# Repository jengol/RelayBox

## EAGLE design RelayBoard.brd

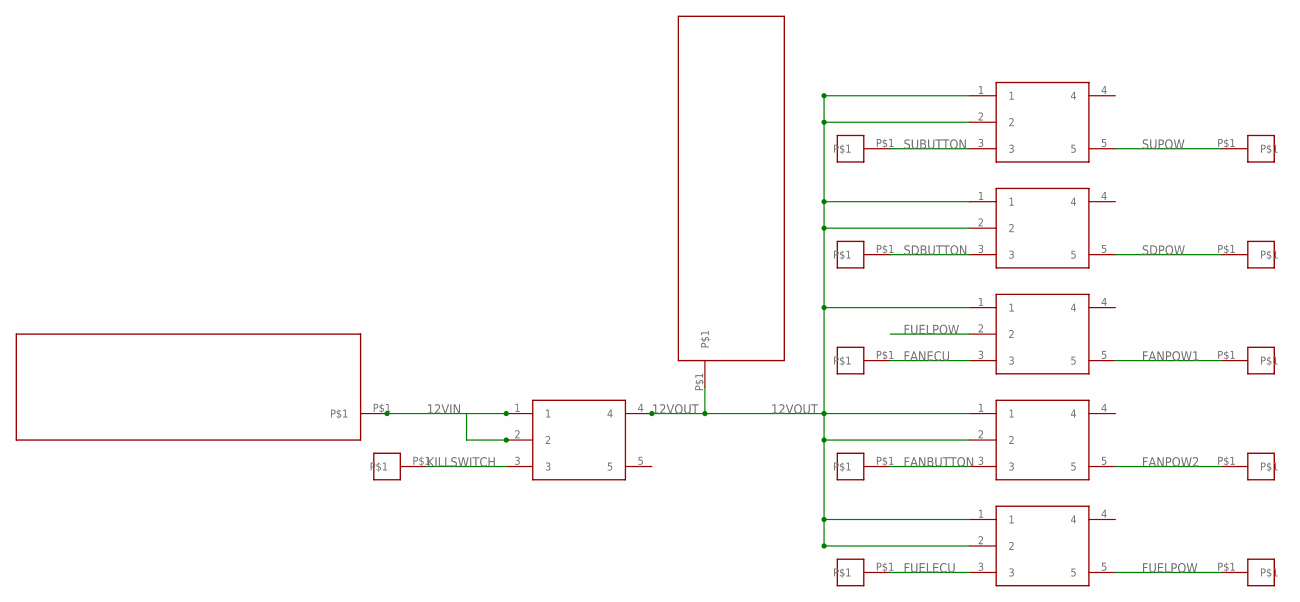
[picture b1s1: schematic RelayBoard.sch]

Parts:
U$1, U$2, U$3, U$4, U$5, U$6: RELAY
U$7, U$8: PLUG2
U$9, U$10, U$11, U$12, U$13, U$14, U$15, U$16, U$17, U$18, U$19: OUTPUT

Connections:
12VIN: U$6.1, U$6.2, U$7.P$1
12VOUT: U$1.1, U$1.2, U$2.1, U$2.2, U$3.1, U$4.1, U$4.2, U$5.1, U$5.2, U$6.4, U$8.P$1
FANBUTTON: U$4.3, U$11.P$1
FANECU: U$3.3, U$10.P$1
FANPOW1: U$3.5, U$16.P$1
FANPOW2: U$4.5, U$17.P$1
FUELECU: U$5.3, U$12.P$1
FUELPOW: U$3.2, U$5.5, U$18.P$1
KILLSWITCH: U$6.3, U$19.P$1
SDBUTTON: U$2.3, U$9.P$1
SDPOW: U$2.5, U$15.P$1
SUBUTTON: U$1.3, U$13.P$1
SUPOW: U$1.5, U$14.P$1

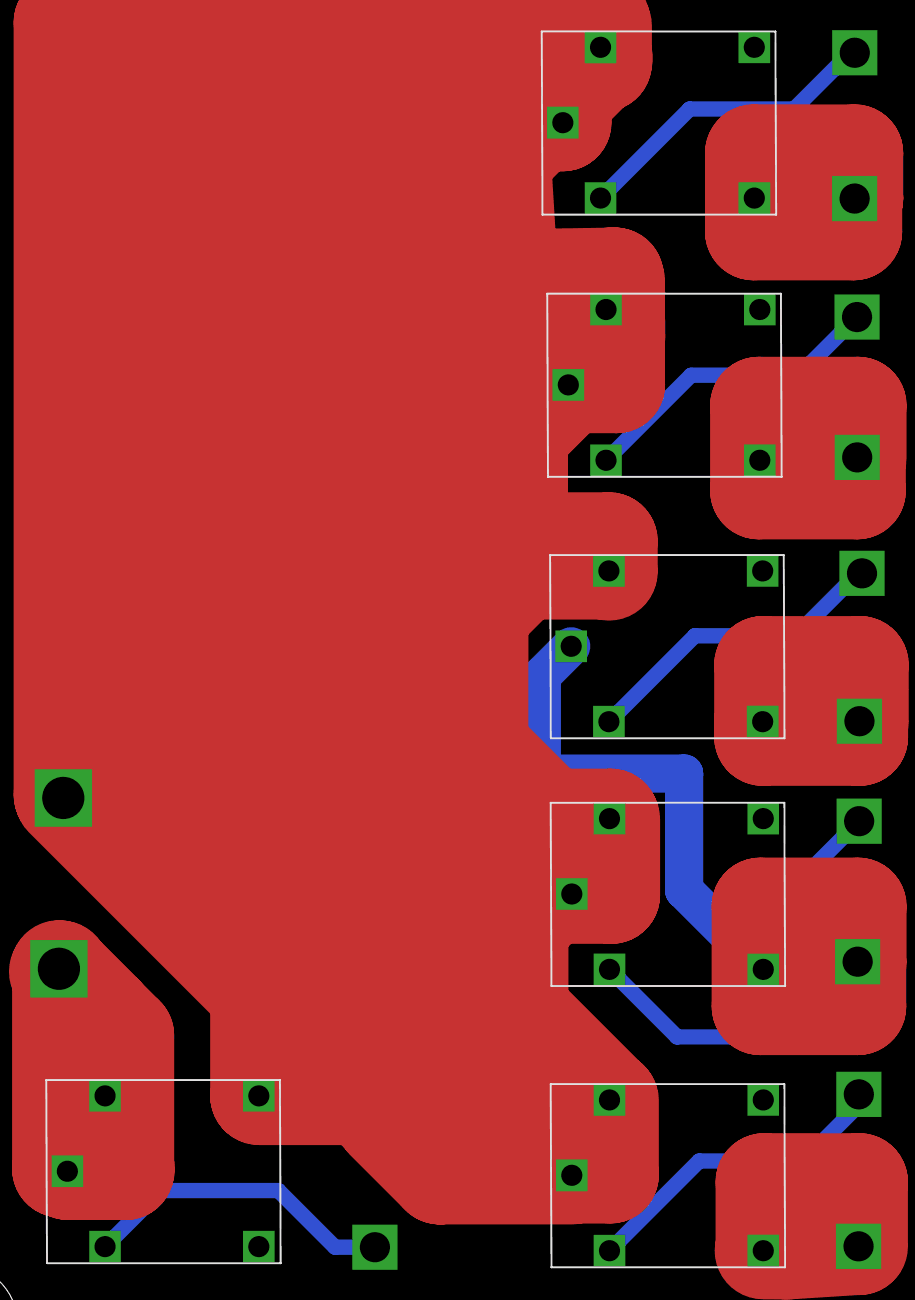
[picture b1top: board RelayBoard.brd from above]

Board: 2 copper layers, 19 parts (0 on the bottom side), 13 nets.

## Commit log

2015-09-25 Inital Commit
